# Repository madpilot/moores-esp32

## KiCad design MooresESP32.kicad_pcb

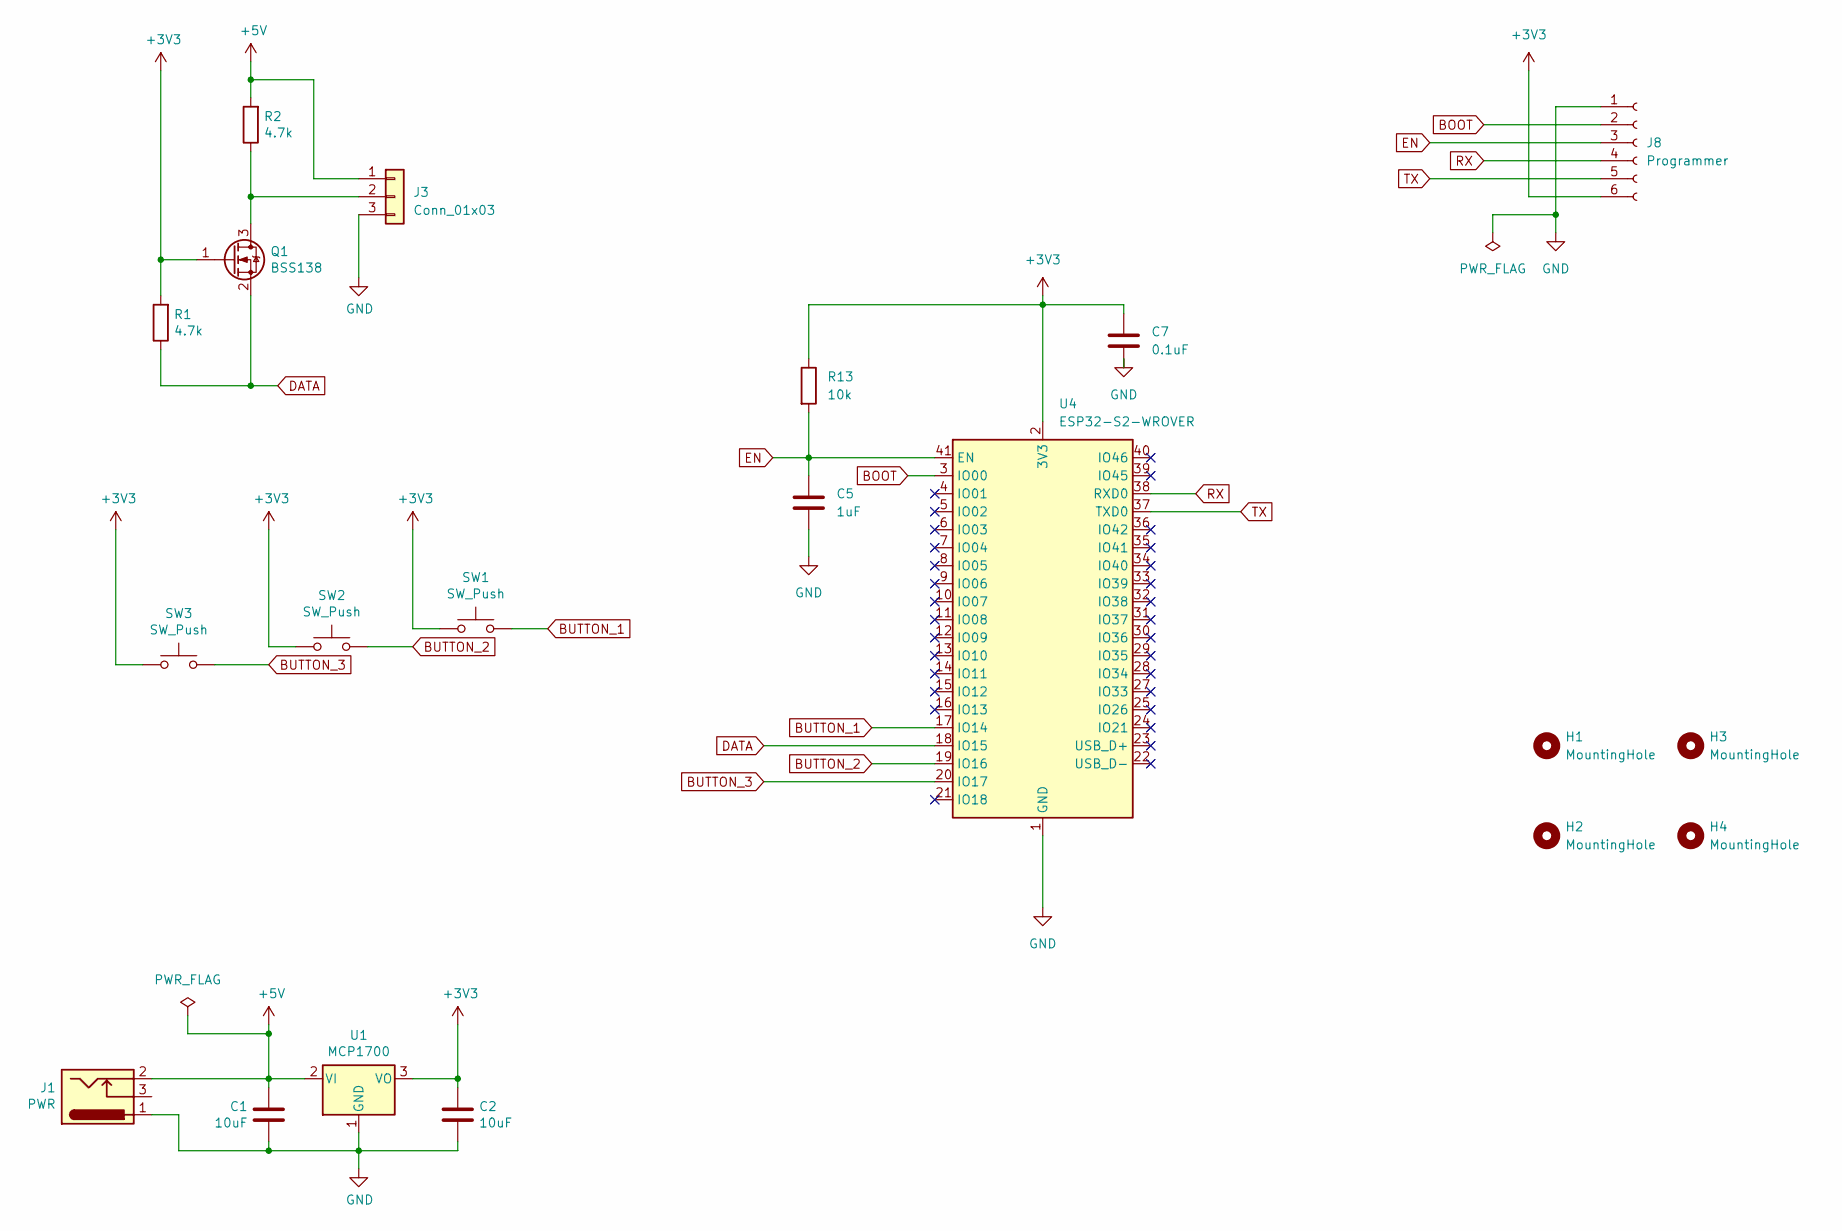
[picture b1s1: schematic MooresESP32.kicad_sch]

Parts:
C1, C2: 10uF; C_0805_2012Metric
C5: 1uF; C_0805_2012Metric
C7: 0.1uF; C_0805_2012Metric
H1, H2, H3, H4: MountingHole; MountingHole_5.5mm
J1: PWR; BarrelJack_Horizontal
J3: Conn_01x03; JST_EH_S3B-EH_1x03_P2.50mm_Horizontal
J8: Programmer; PinHeader_1x06_P2.54mm_Vertical
Q1: BSS138; SOT-23
R1, R2: 4.7k; C_0805_2012Metric
R13: 10k; R_0805_2012Metric
SW1, SW2, SW3: SW_Push; SW_PUSH_6mm
U1: MCP1700; SOT-89-3
U4: ESP32-S2-WROVER

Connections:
+3V3: C2.1, C7.1, J8.6, Q1.1 (G), R1.2, R13.1, SW1.1, SW2.1, SW3.1, U1.3 (VO), U4.2 (3V3)
+5V: C1.1, J1.2, J3.1, R2.2, U1.2 (VI)
BOOT: J8.2, U4.3 (IO00)
BUTTON_1: SW1.2, U4.17 (IO14)
BUTTON_2: SW2.2, U4.19 (IO16)
BUTTON_3: SW3.2, U4.20 (IO17)
DATA: Q1.2 (S), R1.1, U4.18 (IO15)
EN: C5.1, J8.3, R13.2, U4.41 (EN)
GND: C1.2, C2.2, C5.2, C7.2, J1.1, J3.3, J8.1, U1.1 (GND), U4.1 (GND), U4.26 (GND), U4.42 (GND), U4.43 (GND)
unnamed: J3.2, Q1.3 (D), R2.1
RX: J8.4, U4.38 (RXD0)
TX: J8.5, U4.37 (TXD0)

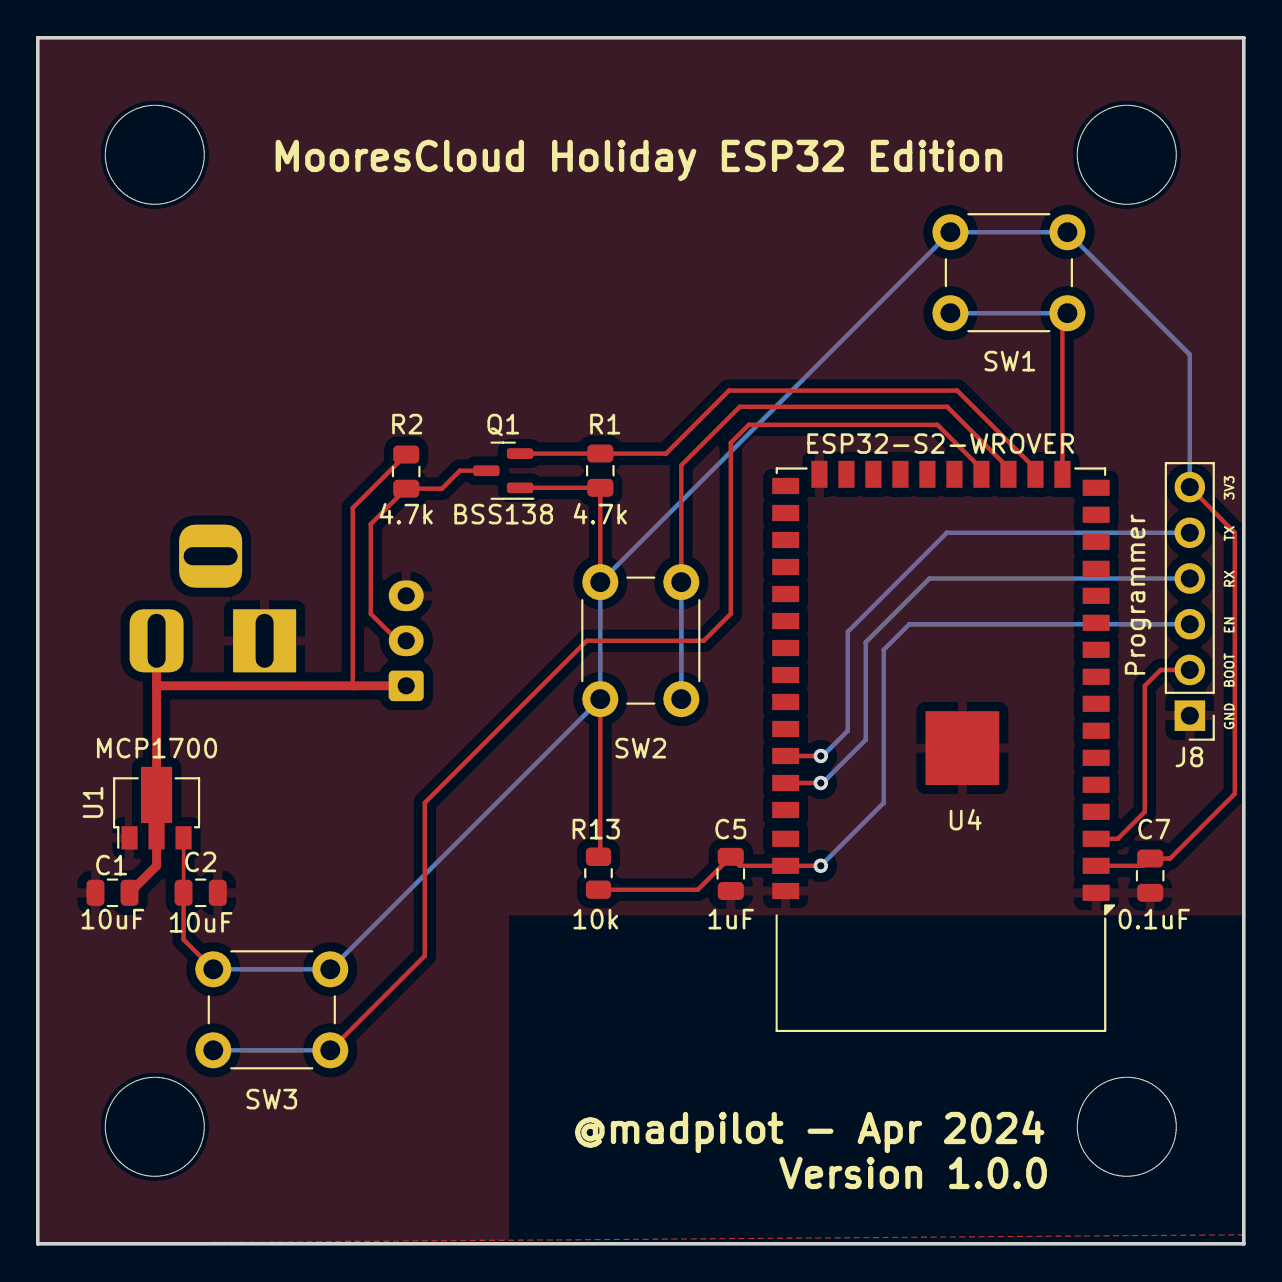
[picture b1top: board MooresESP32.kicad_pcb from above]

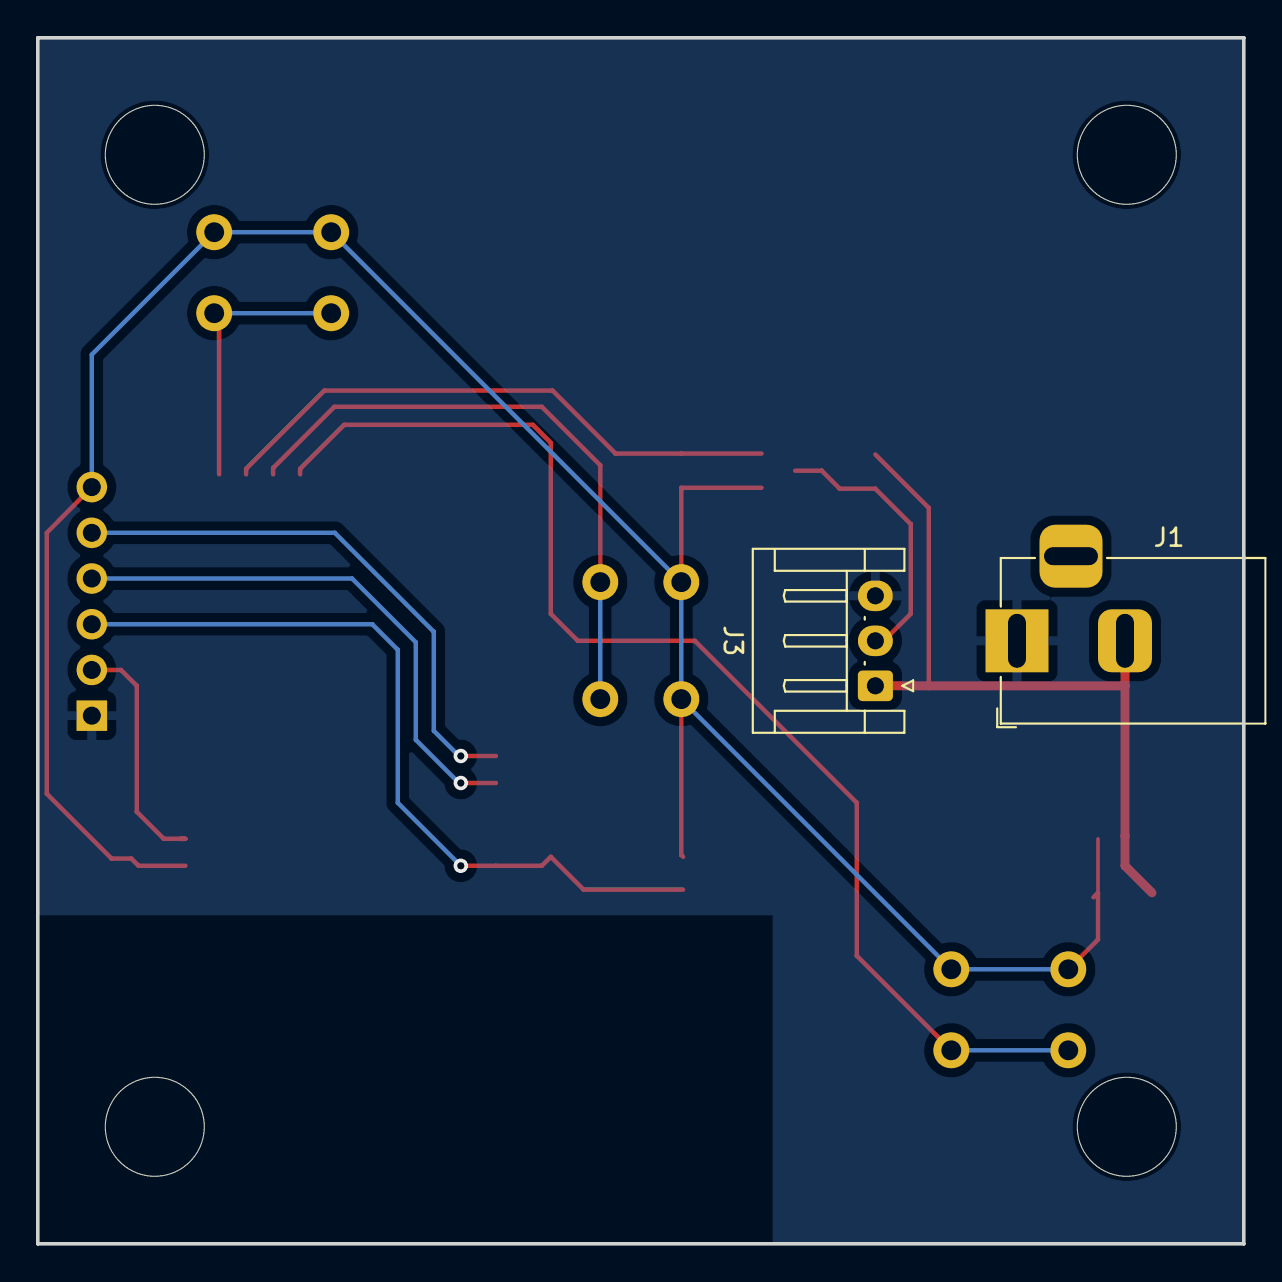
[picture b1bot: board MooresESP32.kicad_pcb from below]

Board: 2 copper layers, 67.0 x 67.0 mm, 20 parts (2 on the bottom side), 12 nets.

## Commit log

2025-04-27 Initial check in
2025-04-28 Updating to KiCAD 8
2025-05-08 Add Gerbers
